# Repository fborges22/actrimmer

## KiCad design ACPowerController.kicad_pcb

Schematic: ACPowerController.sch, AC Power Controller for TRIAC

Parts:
C1: 0.01uF; C_Rect_L7_W2.5_P5
D1: BT139-800; TO-220_Neutral123_Horizontal
P1: UCCONN; Pin_Header_Angled_1x02
P2: ACBUS; bornier2
P3: LOAD; bornier2
R1, R2, R3: 330; Resistor_Horizontal_RM7mm
R4: 39; Resistor_Horizontal_RM7mm
U1: MOC3061M

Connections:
GND: P1.1, U1.2
unnamed: C1.1, R4.1
unnamed: C1.2, D1.2 (A2), P3.2, R2.1
unnamed: D1.1 (A1), P2.1, R3.1, R4.2
unnamed: D1.3 (G), R2.2, U1.4
unnamed: P1.2, R1.2
unnamed: P2.2, P3.1
unnamed: R1.1, U1.1
unnamed: R3.2, U1.6

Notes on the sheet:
AC Power Controller Circuit for TRIAC use

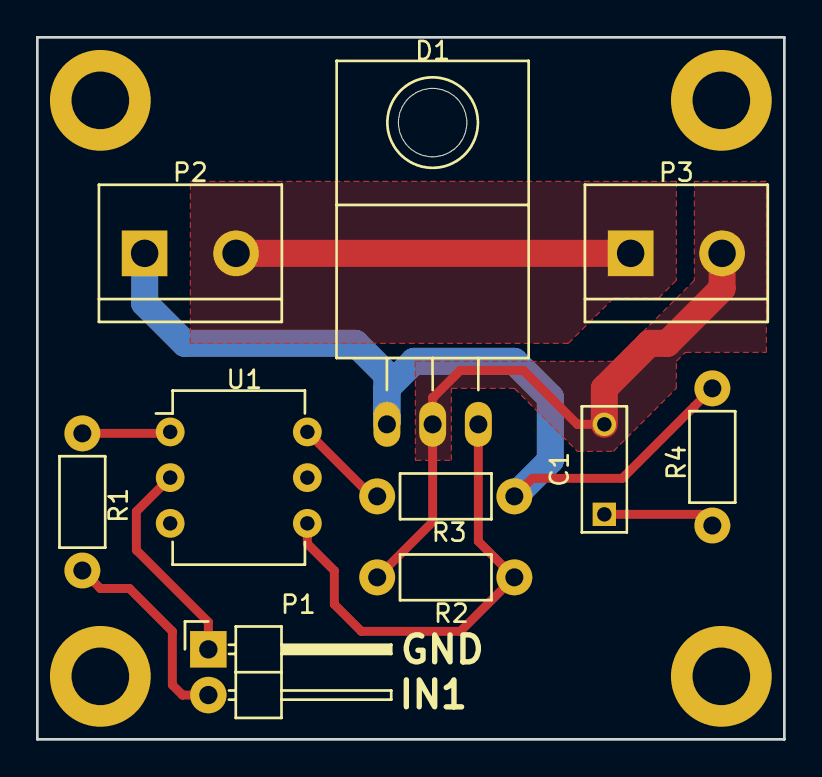
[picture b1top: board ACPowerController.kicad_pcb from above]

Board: 2 copper layers, 41.5 x 39.0 mm, 10 parts (0 on the bottom side), 9 nets.

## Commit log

2019-02-05 First commit of the AC Power Controller with TRIAC.
